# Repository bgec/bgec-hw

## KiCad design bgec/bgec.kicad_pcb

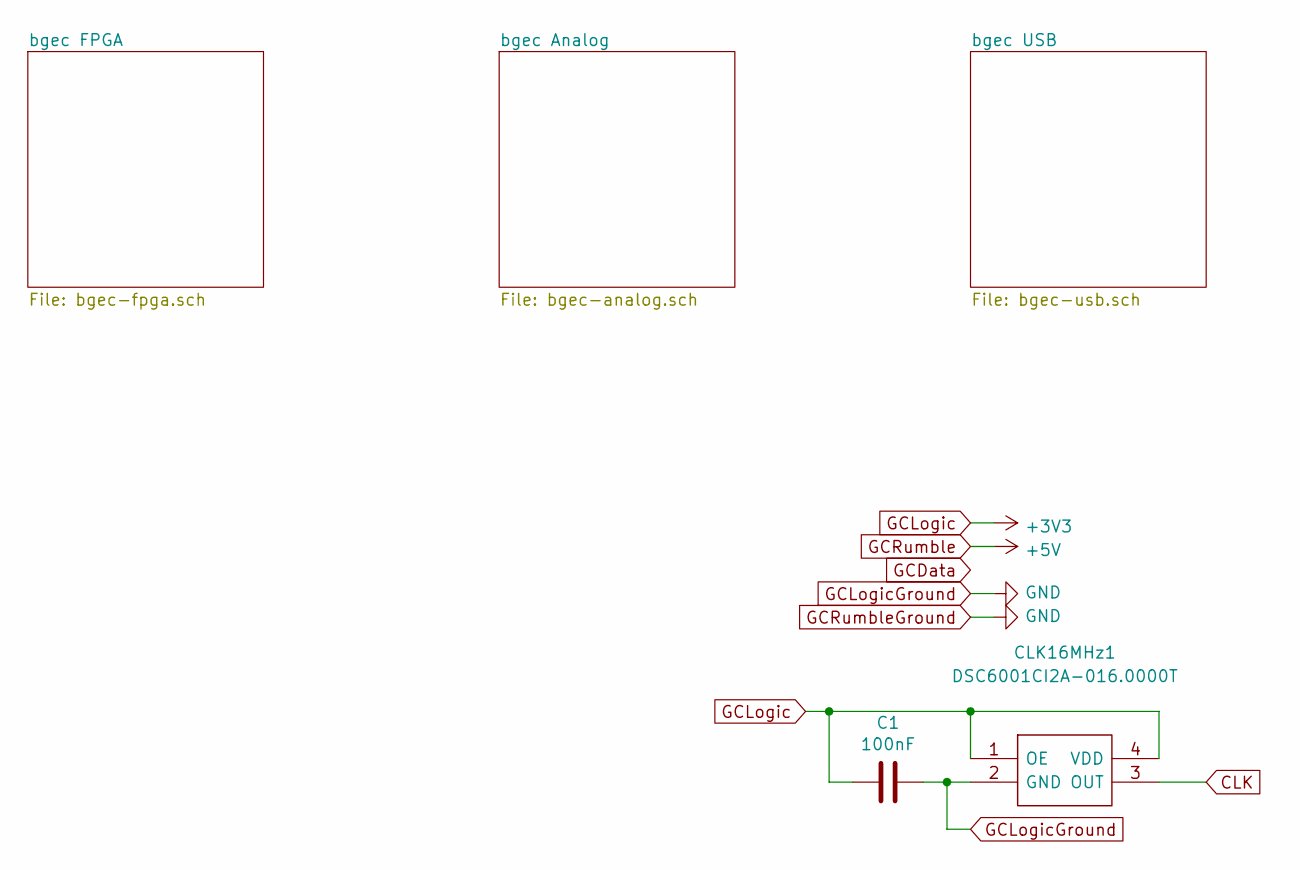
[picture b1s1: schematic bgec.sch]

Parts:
C1: 100nF; C_0402_1005Metric
CLK16MHz1: DSC6001CI2A-016.0000T; 4-LEAD_CDFN-3.2X2.5_1; Mouser Part Number 579-6001CI2A0160000T

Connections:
CLK: CLK16MHz1.3 (OUT); also elsewhere on the board
GCLogic: C1.1, CLK16MHz1.1 (OE), CLK16MHz1.4 (VDD); also elsewhere on the board
GCLogicGround: C1.2, CLK16MHz1.2 (GND); also elsewhere on the board

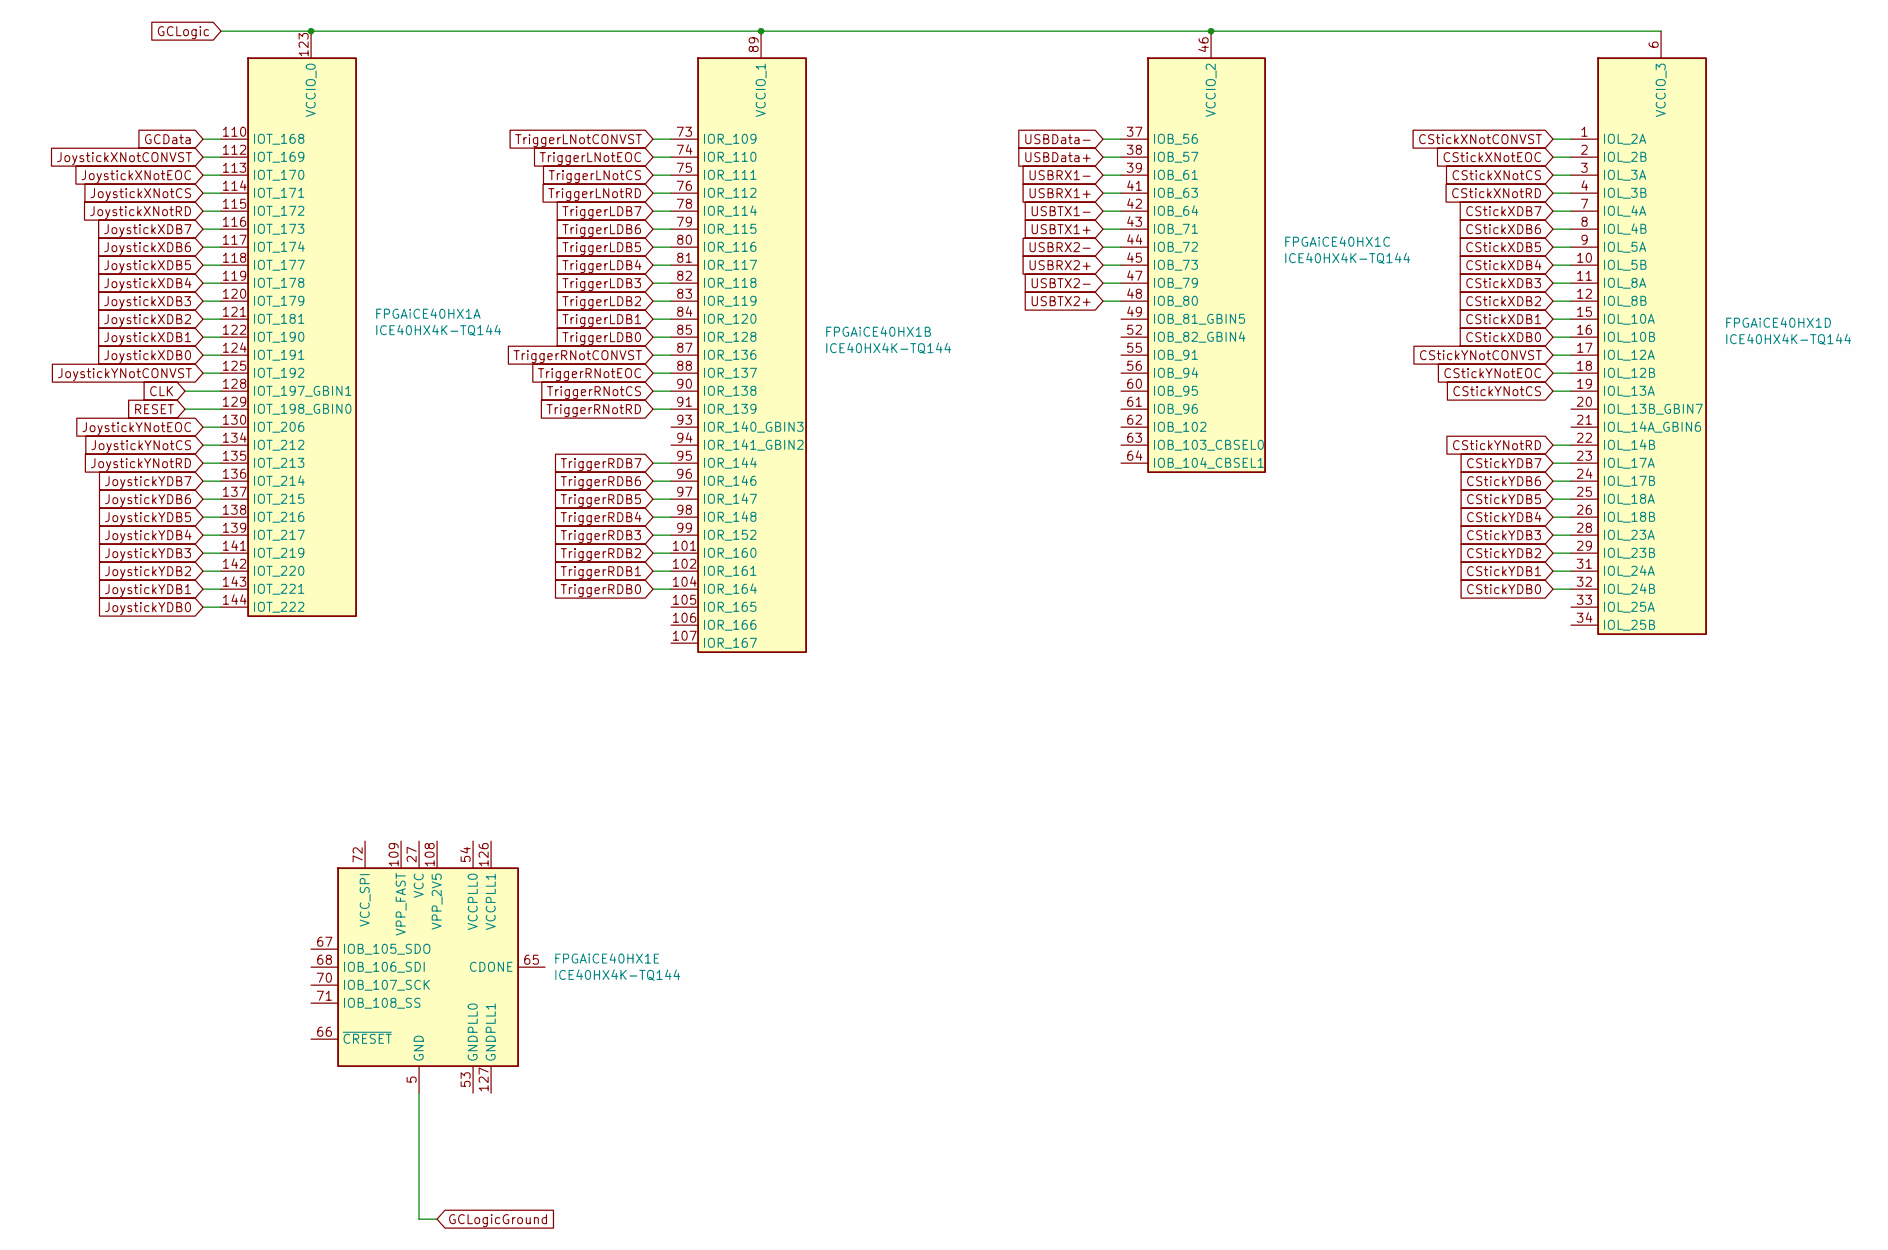
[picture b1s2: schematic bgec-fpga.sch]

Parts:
FPGAiCE40HX1: ICE40HX4K-TQ144; TQFP-144_20x20mm_P0.5mm

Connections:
CLK: FPGAiCE40HX1.128 (IOT_197_GBIN1); also elsewhere on the board
CStickXDB0: FPGAiCE40HX1.16 (IOL_10B); also elsewhere on the board
CStickXDB1: FPGAiCE40HX1.15 (IOL_10A); also elsewhere on the board
CStickXDB2: FPGAiCE40HX1.12 (IOL_8B); also elsewhere on the board
CStickXDB3: FPGAiCE40HX1.11 (IOL_8A); also elsewhere on the board
CStickXDB4: FPGAiCE40HX1.10 (IOL_5B); also elsewhere on the board
CStickXDB5: FPGAiCE40HX1.9 (IOL_5A); also elsewhere on the board
CStickXDB6: FPGAiCE40HX1.8 (IOL_4B); also elsewhere on the board
CStickXDB7: FPGAiCE40HX1.7 (IOL_4A); also elsewhere on the board
CStickXNotCONVST: FPGAiCE40HX1.1 (IOL_2A); also elsewhere on the board
CStickXNotCS: FPGAiCE40HX1.3 (IOL_3A); also elsewhere on the board
CStickXNotEOC: FPGAiCE40HX1.2 (IOL_2B); also elsewhere on the board
CStickXNotRD: FPGAiCE40HX1.4 (IOL_3B); also elsewhere on the board
CStickYDB0: FPGAiCE40HX1.32 (IOL_24B); also elsewhere on the board
CStickYDB1: FPGAiCE40HX1.31 (IOL_24A); also elsewhere on the board
CStickYDB2: FPGAiCE40HX1.29 (IOL_23B); also elsewhere on the board
CStickYDB3: FPGAiCE40HX1.28 (IOL_23A); also elsewhere on the board
CStickYDB4: FPGAiCE40HX1.26 (IOL_18B); also elsewhere on the board
CStickYDB5: FPGAiCE40HX1.25 (IOL_18A); also elsewhere on the board
CStickYDB6: FPGAiCE40HX1.24 (IOL_17B); also elsewhere on the board
CStickYDB7: FPGAiCE40HX1.23 (IOL_17A); also elsewhere on the board
CStickYNotCONVST: FPGAiCE40HX1.17 (IOL_12A); also elsewhere on the board
CStickYNotCS: FPGAiCE40HX1.19 (IOL_13A); also elsewhere on the board
CStickYNotEOC: FPGAiCE40HX1.18 (IOL_12B); also elsewhere on the board
CStickYNotRD: FPGAiCE40HX1.22 (IOL_14B); also elsewhere on the board
GCData: FPGAiCE40HX1.110 (IOT_168)
GCLogic: FPGAiCE40HX1.6 (VCCIO_3), FPGAiCE40HX1.30 (VCCIO_3), FPGAiCE40HX1.46 (VCCIO_2), FPGAiCE40HX1.57 (VCCIO_2), FPGAiCE40HX1.89 (VCCIO_1), FPGAiCE40HX1.100 (VCCIO_1), FPGAiCE40HX1.123 (VCCIO_0), FPGAiCE40HX1.131 (VCCIO_0); also elsewhere on the board
GCLogicGround: FPGAiCE40HX1.5 (GND), FPGAiCE40HX1.13 (GND), FPGAiCE40HX1.14 (GND), FPGAiCE40HX1.59 (GND), FPGAiCE40HX1.69 (GND), FPGAiCE40HX1.86 (GND), FPGAiCE40HX1.103 (GND), FPGAiCE40HX1.132 (GND), FPGAiCE40HX1.140 (GND); also elsewhere on the board
JoystickXDB0: FPGAiCE40HX1.124 (IOT_191); also elsewhere on the board
JoystickXDB1: FPGAiCE40HX1.122 (IOT_190); also elsewhere on the board
JoystickXDB2: FPGAiCE40HX1.121 (IOT_181); also elsewhere on the board
JoystickXDB3: FPGAiCE40HX1.120 (IOT_179); also elsewhere on the board
JoystickXDB4: FPGAiCE40HX1.119 (IOT_178); also elsewhere on the board
JoystickXDB5: FPGAiCE40HX1.118 (IOT_177); also elsewhere on the board
JoystickXDB6: FPGAiCE40HX1.117 (IOT_174); also elsewhere on the board
JoystickXDB7: FPGAiCE40HX1.116 (IOT_173); also elsewhere on the board
JoystickXNotCONVST: FPGAiCE40HX1.112 (IOT_169); also elsewhere on the board
JoystickXNotCS: FPGAiCE40HX1.114 (IOT_171); also elsewhere on the board
JoystickXNotEOC: FPGAiCE40HX1.113 (IOT_170); also elsewhere on the board
JoystickXNotRD: FPGAiCE40HX1.115 (IOT_172); also elsewhere on the board
JoystickYDB0: FPGAiCE40HX1.144 (IOT_222); also elsewhere on the board
JoystickYDB1: FPGAiCE40HX1.143 (IOT_221); also elsewhere on the board
JoystickYDB2: FPGAiCE40HX1.142 (IOT_220); also elsewhere on the board
JoystickYDB3: FPGAiCE40HX1.141 (IOT_219); also elsewhere on the board
JoystickYDB4: FPGAiCE40HX1.139 (IOT_217); also elsewhere on the board
JoystickYDB5: FPGAiCE40HX1.138 (IOT_216); also elsewhere on the board
JoystickYDB6: FPGAiCE40HX1.137 (IOT_215); also elsewhere on the board
JoystickYDB7: FPGAiCE40HX1.136 (IOT_214); also elsewhere on the board
JoystickYNotCONVST: FPGAiCE40HX1.125 (IOT_192); also elsewhere on the board
JoystickYNotCS: FPGAiCE40HX1.134 (IOT_212); also elsewhere on the board
JoystickYNotEOC: FPGAiCE40HX1.130 (IOT_206); also elsewhere on the board
JoystickYNotRD: FPGAiCE40HX1.135 (IOT_213); also elsewhere on the board
unnamed: FPGAiCE40HX1.27 (VCC), FPGAiCE40HX1.40 (VCC), FPGAiCE40HX1.92 (VCC), FPGAiCE40HX1.111 (VCC)
RESET: FPGAiCE40HX1.129 (IOT_198_GBIN0)
TriggerLDB0: FPGAiCE40HX1.85 (IOR_128); also elsewhere on the board
TriggerLDB1: FPGAiCE40HX1.84 (IOR_120); also elsewhere on the board
TriggerLDB2: FPGAiCE40HX1.83 (IOR_119); also elsewhere on the board
TriggerLDB3: FPGAiCE40HX1.82 (IOR_118); also elsewhere on the board
TriggerLDB4: FPGAiCE40HX1.81 (IOR_117); also elsewhere on the board
TriggerLDB5: FPGAiCE40HX1.80 (IOR_116); also elsewhere on the board
TriggerLDB6: FPGAiCE40HX1.79 (IOR_115); also elsewhere on the board
TriggerLDB7: FPGAiCE40HX1.78 (IOR_114); also elsewhere on the board
TriggerLNotCONVST: FPGAiCE40HX1.73 (IOR_109); also elsewhere on the board
TriggerLNotCS: FPGAiCE40HX1.75 (IOR_111); also elsewhere on the board
TriggerLNotEOC: FPGAiCE40HX1.74 (IOR_110); also elsewhere on the board
TriggerLNotRD: FPGAiCE40HX1.76 (IOR_112); also elsewhere on the board
TriggerRDB0: FPGAiCE40HX1.104 (IOR_164); also elsewhere on the board
TriggerRDB1: FPGAiCE40HX1.102 (IOR_161); also elsewhere on the board
TriggerRDB2: FPGAiCE40HX1.101 (IOR_160); also elsewhere on the board
TriggerRDB3: FPGAiCE40HX1.99 (IOR_152); also elsewhere on the board
TriggerRDB4: FPGAiCE40HX1.98 (IOR_148); also elsewhere on the board
TriggerRDB5: FPGAiCE40HX1.97 (IOR_147); also elsewhere on the board
TriggerRDB6: FPGAiCE40HX1.96 (IOR_146); also elsewhere on the board
TriggerRDB7: FPGAiCE40HX1.95 (IOR_144); also elsewhere on the board
TriggerRNotCONVST: FPGAiCE40HX1.87 (IOR_136); also elsewhere on the board
TriggerRNotCS: FPGAiCE40HX1.90 (IOR_138); also elsewhere on the board
TriggerRNotEOC: FPGAiCE40HX1.88 (IOR_137); also elsewhere on the board
TriggerRNotRD: FPGAiCE40HX1.91 (IOR_139); also elsewhere on the board
USBData+: FPGAiCE40HX1.38 (IOB_57); also elsewhere on the board
USBData-: FPGAiCE40HX1.37 (IOB_56); also elsewhere on the board
USBRX1+: FPGAiCE40HX1.41 (IOB_63); also elsewhere on the board
USBRX1-: FPGAiCE40HX1.39 (IOB_61); also elsewhere on the board
USBRX2+: FPGAiCE40HX1.45 (IOB_73); also elsewhere on the board
USBRX2-: FPGAiCE40HX1.44 (IOB_72); also elsewhere on the board
USBTX1+: FPGAiCE40HX1.43 (IOB_71); also elsewhere on the board
USBTX1-: FPGAiCE40HX1.42 (IOB_64); also elsewhere on the board
USBTX2+: FPGAiCE40HX1.48 (IOB_80); also elsewhere on the board
USBTX2-: FPGAiCE40HX1.47 (IOB_79); also elsewhere on the board

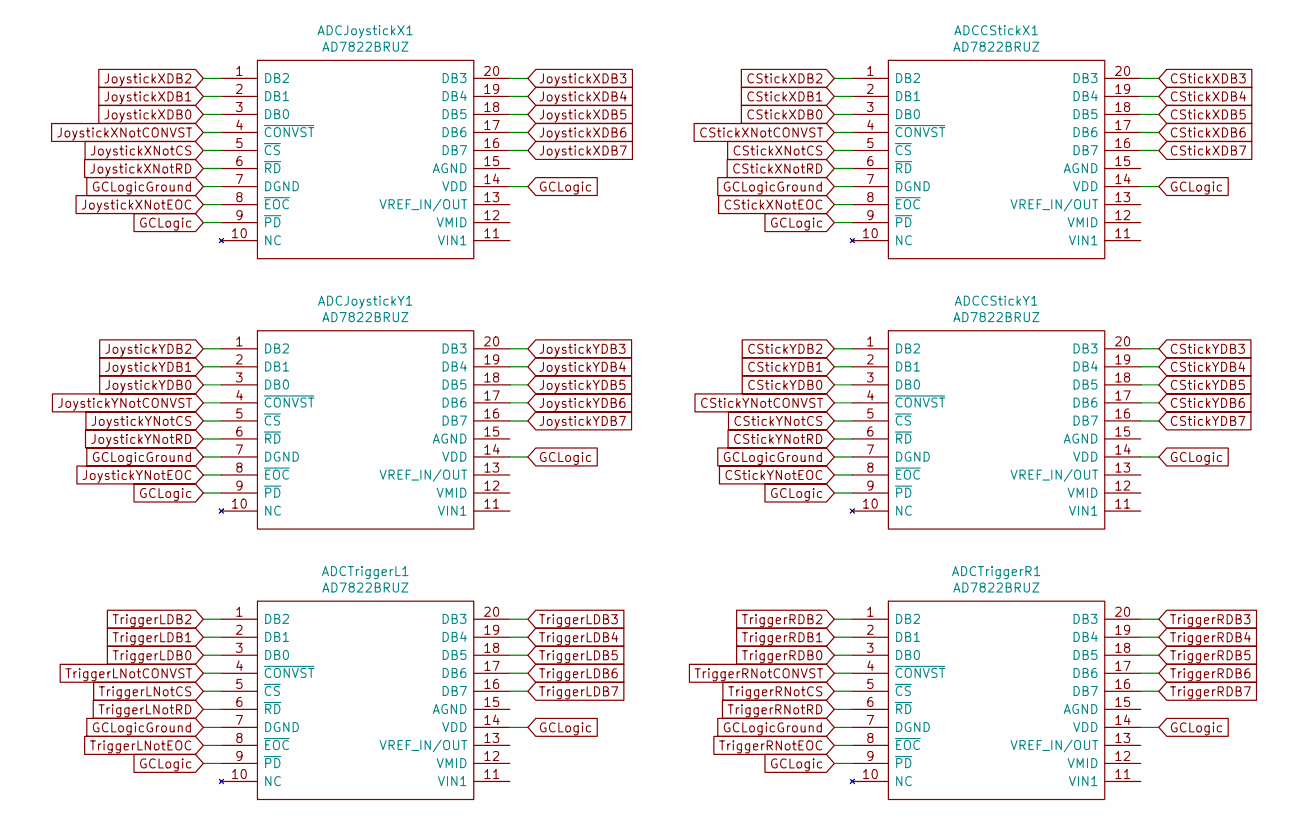
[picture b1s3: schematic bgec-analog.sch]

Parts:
ADCCStickX1: AD7822BRUZ; SOP65P640X120-20N; Mouser Part Number 584-AD7822BRUZ
ADCCStickY1: AD7822BRUZ; SOP65P640X120-20N; Mouser Part Number 584-AD7822BRUZ
ADCJoystickX1: AD7822BRUZ; SOP65P640X120-20N; Mouser Part Number 584-AD7822BRUZ
ADCJoystickY1: AD7822BRUZ; SOP65P640X120-20N; Mouser Part Number 584-AD7822BRUZ
ADCTriggerL1: AD7822BRUZ; SOP65P640X120-20N; Mouser Part Number 584-AD7822BRUZ
ADCTriggerR1: AD7822BRUZ; SOP65P640X120-20N; Mouser Part Number 584-AD7822BRUZ

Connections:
CStickXDB0: ADCCStickX1.3 (DB0); also elsewhere on the board
CStickXDB1: ADCCStickX1.2 (DB1); also elsewhere on the board
CStickXDB2: ADCCStickX1.1 (DB2); also elsewhere on the board
CStickXDB3: ADCCStickX1.20 (DB3); also elsewhere on the board
CStickXDB4: ADCCStickX1.19 (DB4); also elsewhere on the board
CStickXDB5: ADCCStickX1.18 (DB5); also elsewhere on the board
CStickXDB6: ADCCStickX1.17 (DB6); also elsewhere on the board
CStickXDB7: ADCCStickX1.16 (DB7); also elsewhere on the board
CStickXNotCONVST: ADCCStickX1.4 (~CONVST); also elsewhere on the board
CStickXNotCS: ADCCStickX1.5 (~CS); also elsewhere on the board
CStickXNotEOC: ADCCStickX1.8 (~EOC); also elsewhere on the board
CStickXNotRD: ADCCStickX1.6 (~RD); also elsewhere on the board
CStickYDB0: ADCCStickY1.3 (DB0); also elsewhere on the board
CStickYDB1: ADCCStickY1.2 (DB1); also elsewhere on the board
CStickYDB2: ADCCStickY1.1 (DB2); also elsewhere on the board
CStickYDB3: ADCCStickY1.20 (DB3); also elsewhere on the board
CStickYDB4: ADCCStickY1.19 (DB4); also elsewhere on the board
CStickYDB5: ADCCStickY1.18 (DB5); also elsewhere on the board
CStickYDB6: ADCCStickY1.17 (DB6); also elsewhere on the board
CStickYDB7: ADCCStickY1.16 (DB7); also elsewhere on the board
CStickYNotCONVST: ADCCStickY1.4 (~CONVST); also elsewhere on the board
CStickYNotCS: ADCCStickY1.5 (~CS); also elsewhere on the board
CStickYNotEOC: ADCCStickY1.8 (~EOC); also elsewhere on the board
CStickYNotRD: ADCCStickY1.6 (~RD); also elsewhere on the board
GCLogic: ADCCStickX1.9 (~PD), ADCCStickX1.14 (VDD), ADCCStickY1.9 (~PD), ADCCStickY1.14 (VDD), ADCJoystickX1.9 (~PD), ADCJoystickX1.14 (VDD), ADCJoystickY1.9 (~PD), ADCJoystickY1.14 (VDD), ADCTriggerL1.9 (~PD), ADCTriggerL1.14 (VDD), ADCTriggerR1.9 (~PD), ADCTriggerR1.14 (VDD); also elsewhere on the board
GCLogicGround: ADCCStickX1.7 (DGND), ADCCStickY1.7 (DGND), ADCJoystickX1.7 (DGND), ADCJoystickY1.7 (DGND), ADCTriggerL1.7 (DGND), ADCTriggerR1.7 (DGND); also elsewhere on the board
JoystickXDB0: ADCJoystickX1.3 (DB0); also elsewhere on the board
JoystickXDB1: ADCJoystickX1.2 (DB1); also elsewhere on the board
JoystickXDB2: ADCJoystickX1.1 (DB2); also elsewhere on the board
JoystickXDB3: ADCJoystickX1.20 (DB3); also elsewhere on the board
JoystickXDB4: ADCJoystickX1.19 (DB4); also elsewhere on the board
JoystickXDB5: ADCJoystickX1.18 (DB5); also elsewhere on the board
JoystickXDB6: ADCJoystickX1.17 (DB6); also elsewhere on the board
JoystickXDB7: ADCJoystickX1.16 (DB7); also elsewhere on the board
JoystickXNotCONVST: ADCJoystickX1.4 (~CONVST); also elsewhere on the board
JoystickXNotCS: ADCJoystickX1.5 (~CS); also elsewhere on the board
JoystickXNotEOC: ADCJoystickX1.8 (~EOC); also elsewhere on the board
JoystickXNotRD: ADCJoystickX1.6 (~RD); also elsewhere on the board
JoystickYDB0: ADCJoystickY1.3 (DB0); also elsewhere on the board
JoystickYDB1: ADCJoystickY1.2 (DB1); also elsewhere on the board
JoystickYDB2: ADCJoystickY1.1 (DB2); also elsewhere on the board
JoystickYDB3: ADCJoystickY1.20 (DB3); also elsewhere on the board
JoystickYDB4: ADCJoystickY1.19 (DB4); also elsewhere on the board
JoystickYDB5: ADCJoystickY1.18 (DB5); also elsewhere on the board
JoystickYDB6: ADCJoystickY1.17 (DB6); also elsewhere on the board
JoystickYDB7: ADCJoystickY1.16 (DB7); also elsewhere on the board
JoystickYNotCONVST: ADCJoystickY1.4 (~CONVST); also elsewhere on the board
JoystickYNotCS: ADCJoystickY1.5 (~CS); also elsewhere on the board
JoystickYNotEOC: ADCJoystickY1.8 (~EOC); also elsewhere on the board
JoystickYNotRD: ADCJoystickY1.6 (~RD); also elsewhere on the board
TriggerLDB0: ADCTriggerL1.3 (DB0); also elsewhere on the board
TriggerLDB1: ADCTriggerL1.2 (DB1); also elsewhere on the board
TriggerLDB2: ADCTriggerL1.1 (DB2); also elsewhere on the board
TriggerLDB3: ADCTriggerL1.20 (DB3); also elsewhere on the board
TriggerLDB4: ADCTriggerL1.19 (DB4); also elsewhere on the board
TriggerLDB5: ADCTriggerL1.18 (DB5); also elsewhere on the board
TriggerLDB6: ADCTriggerL1.17 (DB6); also elsewhere on the board
TriggerLDB7: ADCTriggerL1.16 (DB7); also elsewhere on the board
TriggerLNotCONVST: ADCTriggerL1.4 (~CONVST); also elsewhere on the board
TriggerLNotCS: ADCTriggerL1.5 (~CS); also elsewhere on the board
TriggerLNotEOC: ADCTriggerL1.8 (~EOC); also elsewhere on the board
TriggerLNotRD: ADCTriggerL1.6 (~RD); also elsewhere on the board
TriggerRDB0: ADCTriggerR1.3 (DB0); also elsewhere on the board
TriggerRDB1: ADCTriggerR1.2 (DB1); also elsewhere on the board
TriggerRDB2: ADCTriggerR1.1 (DB2); also elsewhere on the board
TriggerRDB3: ADCTriggerR1.20 (DB3); also elsewhere on the board
TriggerRDB4: ADCTriggerR1.19 (DB4); also elsewhere on the board
TriggerRDB5: ADCTriggerR1.18 (DB5); also elsewhere on the board
TriggerRDB6: ADCTriggerR1.17 (DB6); also elsewhere on the board
TriggerRDB7: ADCTriggerR1.16 (DB7); also elsewhere on the board
TriggerRNotCONVST: ADCTriggerR1.4 (~CONVST); also elsewhere on the board
TriggerRNotCS: ADCTriggerR1.5 (~CS); also elsewhere on the board
TriggerRNotEOC: ADCTriggerR1.8 (~EOC); also elsewhere on the board
TriggerRNotRD: ADCTriggerR1.6 (~RD); also elsewhere on the board

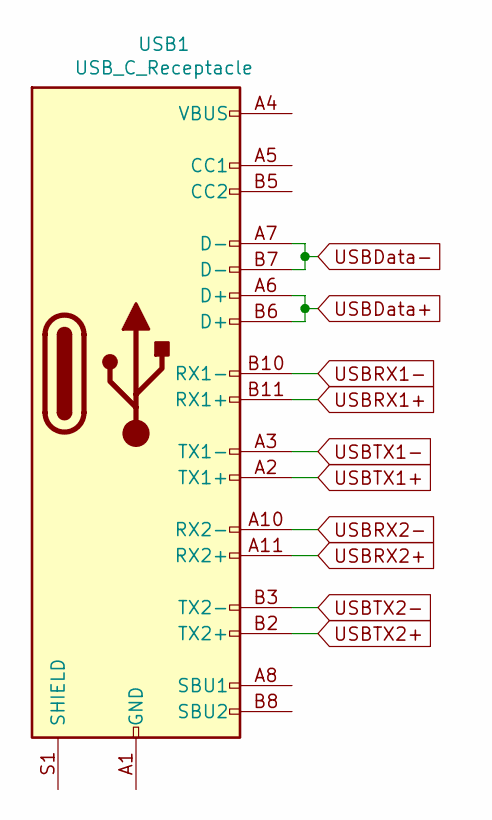
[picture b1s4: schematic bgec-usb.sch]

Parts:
USB1: USB_C_Receptacle; USB_C_Receptacle_Amphenol_12401610E4-2A

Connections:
unnamed: USB1.A1 (GND), USB1.A12 (GND), USB1.B1 (GND), USB1.B12 (GND)
unnamed: USB1.A4 (VBUS), USB1.A9 (VBUS), USB1.B4 (VBUS), USB1.B9 (VBUS)
USBData+: USB1.A6 (D+), USB1.B6 (D+); also elsewhere on the board
USBData-: USB1.A7 (D-), USB1.B7 (D-); also elsewhere on the board
USBRX1+: USB1.B11 (RX1+); also elsewhere on the board
USBRX1-: USB1.B10 (RX1-); also elsewhere on the board
USBRX2+: USB1.A11 (RX2+); also elsewhere on the board
USBRX2-: USB1.A10 (RX2-); also elsewhere on the board
USBTX1+: USB1.A2 (TX1+); also elsewhere on the board
USBTX1-: USB1.A3 (TX1-); also elsewhere on the board
USBTX2+: USB1.B2 (TX2+); also elsewhere on the board
USBTX2-: USB1.B3 (TX2-); also elsewhere on the board

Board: 4 copper layers, 10 parts (0 on the bottom side), 88 nets, no tracks yet.

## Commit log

2020-02-20 Initial commit
    Learning KiCad. It's kind of hard and I'm struggling to understand how TinyFPGA does it (or how I should be doing it personally) but I think I'm on the right track. I'll probably have to look at some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
    Instead of using a TinyFPGA-BX directly in the project, I'm going to overshoot and use a 79 I/O iCE40HX8K-CT256. I have some ambitious ideas about how I want to handle output, especially with the USB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
    My big worry is managing power/voltage. I don't really know how USB works so I'll have to devise a plan to seamlessly switch over
2020-02-20 Add the ADCs for the C Stick
    I need to figure out how to handle having custom parts; they need to be clonable. Additionally, I probably want to have different schematic sheets for different parts of the thing, like a sheet for p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
2020-02-20 Switch to a consistent label style and use better(?) ADCs
    Finding the correct parts to do what I want is hard. On one hand, I want to keep the sample rate high in case a newer protocol needs it, but on the other hand I really don't need anything faster than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
2020-02-21 Start work on splitting and moving external parts to internal lib
2020-02-21 Add second IO bank to the FPGA schematic, move ADC to local library
2020-02-21 Get rid of external references
2020-02-21 Standardize library name and move footprints to local library
2020-02-22 Add clock
2020-02-22 Annotate items so PCB can be generated
2020-02-22 Add clock and reset connections
2020-02-22 Connect the ADCs
    I might be doing this wrong by ignoring CONVST. We'll see. I need to update the software side of things to start doing Parallel ADCs.
2020-02-22 Split into multiple sheets
    Next problem to solve is routing. KiCad and Freerouter really hate that FPGA.
2020-02-22 Switch to official footprint for the FPGA
2020-02-22 Switch to better FPGA for routing
2020-02-22 Add more ADC connections
2020-02-22 Tested freerouter and it worked perfectly
2020-02-23 Properly feed all ADC pins to the FPGA
    Includes rudimentary routing. In the future I'm definitely going to move the ADCs closer to their joysticks/triggers so the model doesn't look like a swastika.
2020-02-23 Remodel ADC placement, add USB-C connector
2020-03-23 Create LICENSE
2020-03-23 Rename LICENSE to LICENSE-CERN
2020-03-23 Create LICENSE-CC-BY-SA
